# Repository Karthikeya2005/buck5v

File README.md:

# buck5v: 12 V to 5 V, 2 A Buck Converter (KiCad 10)

A 2-layer synchronous buck converter board built around the Texas Instruments **TPS54202**. Input is 9 to 24 V, output is 5 V at up to 2 A, with a switching frequency of about 500 kHz.

> **Status: designed and checked in software only.**
> The board has not been fabricated, assembled or measured. Every figure below is a calculation from the datasheet, not a bench result. Part sourcing (stock, LCSC numbers) was not verified either.

I built this to learn power-supply design end to end: choosing the IC, calculating each component, wiring the schematic, laying out the board around the switching loop, and checking it with ERC and DRC. I checked the datasheet values and reviewed the schematic, layout and DRC results myself.

## Specification

| Parameter | Value |
|---|---|
| Input voltage | 9 to 24 V (IC accepts 4.5 to 28 V) |
| Output voltage | 5 V (about 5.03 V typical) |
| Output current | 2 A |
| Switching frequency | 500 kHz typical (390 to 630 kHz) |
| Topology | Synchronous buck, integrated FETs |
| Board | 2 layers, 45 x 35 mm |
| Protection | Series Schottky for reverse polarity, EN divider as undervoltage lockout |

## Design

### IC: TPS54202DDCR
4.5 to 28 V input, 2 A, internal high-side and low-side FETs, so no external catch diode is needed. Datasheet values I used: feedback voltage VFB = 0.596 V (0.581 to 0.611 V), switching frequency 500 kHz, low-side current limit up to 4.3 A.

### Output voltage
Vout = VFB x (1 + R1 / R2) = 0.596 x (1 + 102 k / 13.7 k) = **5.03 V** typical.
Over the VFB tolerance the output spans 4.91 to 5.16 V. Both resistors are standard 1% values.

### Inductor
L = 15 uH (Sunlord MWSA1004S-150MT: 45 mOhm DCR max, Isat 5.6 A taken conservatively from the datasheet).

| Vin | Duty cycle | Ripple current (p-p) | Peak current at 2 A load |
|---|---|---|---|
| 9 V | 0.56 | 0.30 A | 2.15 A |
| 12 V | 0.42 | 0.39 A | 2.19 A |
| 24 V | 0.21 | 0.53 A | 2.26 A |

Ripple current = Vout x (1 - D) / (L x f). Peak current stays well below both the inductor's 5.6 A saturation current and the IC's 4.3 A maximum low-side limit.

### Capacitors
| Ref | Value | Role |
|---|---|---|
| C1, C2 | 10 uF 50 V X7R (1210) | Bulk input |
| C3 | 100 nF 50 V X7R (0603) | High-frequency input decoupling, placed at the VIN pin |
| C4 | 100 nF 50 V X7R (0603) | Bootstrap, BOOT to SW |
| C5, C6 | 22 uF 25 V X7R (1210) | Output |
| C7 | 75 pF C0G (0603), not populated | Optional feed-forward across R1 |

Ceramic capacitance falls with DC bias, so the effective output capacitance at 5 V is lower than 44 uF. Output ripple depends mostly on ESR and layout, so it has to be measured on a real board.

### Enable divider (undervoltage lockout)
R4 = 511 k from VIN to EN, R5 = 105 k from EN to GND. With the datasheet EN rising threshold of 1.21 V typical (1.28 V max), the converter starts at about **7.1 V** (7.5 V worst case) at the IC's VIN node. EN sees about 1.5 V at 9 V in and about 4.1 V at 24 V in. Check this against the datasheet's absolute maximum rating for EN before building.

### Reverse-polarity protection
D1 is an SS34 Schottky in series with the input. It costs roughly 0.5 V and about 0.6 W at 9 V in and 2 A out. A P-channel MOSFET would waste less power but needs extra parts.

## Bill of materials

| Ref | Value | Footprint |
|---|---|---|
| U1 | TPS54202DDCR | TSOT-23-6 (hand-solder variant) |
| L1 | 15 uH, MWSA1004S-150MT | Sunlord MWSA1004S |
| D1 | SS34 Schottky | SMA |
| C1, C2 | 10 uF 50 V X7R | 1210 |
| C3, C4 | 100 nF 50 V X7R | 0603 |
| C5, C6 | 22 uF 25 V X7R | 1210 |
| C7 | 75 pF C0G (DNP) | 0603 |
| R1 | 102 k 1% | 0603 |
| R2 | 13.7 k 1% | 0603 |
| R4 | 511 k 1% | 0603 |
| R5 | 105 k 1% | 0603 |
| J1, J2 | 2-pin screw terminal | 5.00 mm pitch |
| TP1 to TP4 | Test points: VIN, VOUT, SW, GND | 1.5 mm pad |

Ordering would need a fresh sourcing pass. Several part numbers (including the inductor) were not confirmed in stock, and the 5.00 mm terminal block should be matched to a real part.

## Layout notes

- The input capacitors sit at the IC's VIN pin. Because SW is between VIN and GND on the 6-pin package, the 100 nF cap's ground return is about 10 mm, so the loop is tight on the VIN side only.
- SW copper is short (about 13 mm in total including the test point). The boot-cap branch off the SW node is about 6 mm, longer than ideal.
- VIN and SW are necked down to 0.65 mm for the first 1.3 to 1.5 mm at the 0.95 mm pin pitch so the 0.25 mm clearance rule holds. Other power traces are 1.0 mm or wider.
- The feedback divider sits near the FB pin, away from SW and L1.
- The bottom layer is a GND plane with stitching vias. The EN trace runs on the bottom layer, short and clear of the switching nodes.
- The TSOT-23-6 has no thermal pad, so heat leaves through the GND pin copper. Thermal performance has not been verified.

## Verification

| Check | Result |
|---|---|
| ERC | 0 errors (PWR_FLAG symbols added to VIN, GND and +5V) |
| DRC | 0 errors, 0 unconnected items at the last run |
| DRC warnings | Mostly stitching vias flagged "not connected on one layer" (the top-layer GND zone only covers a small patch near the IC) and a few silkscreen overlaps |
| Schematic to board sync | No differences |

## Known limitations

- Not built or measured. No efficiency, ripple, thermal or EMI data.
- The top-layer GND pour should cover the whole board. As it stands, the stitching vias outside the patch near U1 only connect to the bottom plane.
- Component sourcing and the 5.00 mm terminal-block part are unverified.
- Ripple and thermal estimates depend on real capacitor ESR and copper area, which this design does not confirm.

## Test plan (if built)

| Test | Setup | What to look for |
|---|---|---|
| Power-up | Bench supply at 12 V, current limit 0.2 A, no load | 5.0 V on TP2, no oscillation or smoke |
| Output accuracy | 9, 12, 24 V in, no load and 2 A load | Output within about +/-3% of 5 V |
| Efficiency | 0.1, 0.25, 0.5, 1, 1.5, 2 A at 9, 12, 24 V | Measure Vin and Iin at the board terminals, Vout and Iout at the load |
| Output ripple | Scope on TP2 with spring ground at TP4, 20 MHz bandwidth | Ripple in mV, compare with the estimate |
| SW waveform | Scope on TP3 | Duty cycle, ringing, frequency near 500 kHz |
| Load step | 0.2 A to 2 A | Overshoot and recovery |
| Thermal | 2 A for 10 minutes, thermal camera or thermocouple | IC and inductor temperature rise |
| Start-up threshold | Slowly raise Vin from 0 | Converter starts near 7 to 7.6 V |

## Repository layout

```
buck5v.kicad_pro        KiCad project
buck5v.kicad_sch        Schematic
buck5v.kicad_pcb        PCB layout
buck5v.kicad_sym        Project symbol library (TPS54202)
sym-lib-table           Library table for the project symbol
docs/                   Images of the schematic, board and 3D view
fab/                    Gerber files, drill files and BOM (CSV)
buck5v-gerbers.zip      The fab/ folder zipped, ready to upload to a board house
```

Open `buck5v.kicad_pro` in KiCad 10 or newer.

## Tools

KiCad 10. Datasheet values were checked by hand against the TI TPS54202 and Sunlord MWSA-S datasheets.

## License

MIT. See [LICENSE](LICENSE). There is no warranty, and nobody has independently reviewed this design. Have it reviewed before building it or using it in anything that matters.

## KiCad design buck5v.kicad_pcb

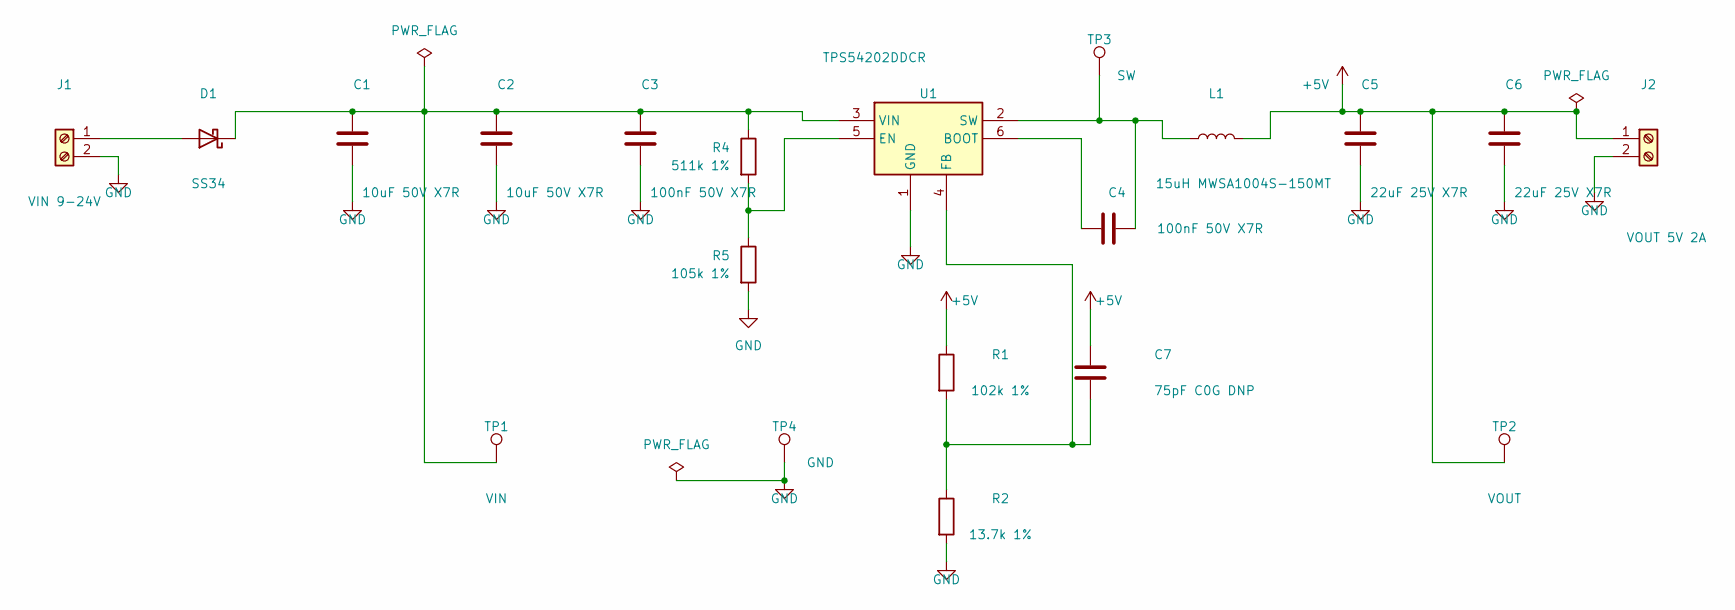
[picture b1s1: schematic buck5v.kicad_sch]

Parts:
C1, C2: 10uF 50V X7R; C_1210_3225Metric; MPN CL32B106KBJNNNE; LCSC C138687
C3, C4: 100nF 50V X7R; C_0603_1608Metric; MPN CL10B104KB8NNNC; LCSC C1591
C5, C6: 22uF 25V X7R; C_1210_3225Metric; MPN CL32B226KAJNNNE; LCSC C309062
C7: 75pF C0G DNP; C_0603_1608Metric
D1: SS34; D_SMA
J1: VIN 9-24V; TerminalBlock_MaiXu_MX126-5.0-02P_1x02_P5.00mm
J2: VOUT 5V 2A; TerminalBlock_MaiXu_MX126-5.0-02P_1x02_P5.00mm
L1: 15uH MWSA1004S-150MT; L_Sunlord_MWSA1004S; MPN MWSA1004S-150MT
R1: 102k 1%; R_0603_1608Metric
R2: 13.7k 1%; R_0603_1608Metric
R4: 511k 1%; R_0603_1608Metric
R5: 105k 1%; R_0603_1608Metric
TP1: VIN; TestPoint_Pad_D1.5mm
TP2: VOUT; TestPoint_Pad_D1.5mm
TP3: SW; TestPoint_Pad_D1.5mm
TP4: GND; TestPoint_Pad_D1.5mm
U1: TPS54202DDCR; TSOT-23-6_HandSoldering; MPN TPS54202DDCR; LCSC C191884

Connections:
+5V: C5.1, C6.1, C7.1, J2.1, L1.2, R1.1, TP2.1
GND: C1.2, C2.2, C3.2, C5.2, C6.2, J1.2, J2.2, R2.2, R5.2, TP4.1, U1.1 (GND)
unnamed: C1.1, C2.1, C3.1, D1.1 (K), R4.1, TP1.1, U1.3 (VIN)
unnamed: C4.1, U1.6 (BOOT)
unnamed: C4.2, L1.1, TP3.1, U1.2 (SW)
unnamed: C7.2, R1.2, R2.1, U1.4 (FB)
unnamed: D1.2 (A), J1.1
unnamed: R4.2, R5.1, U1.5 (EN)

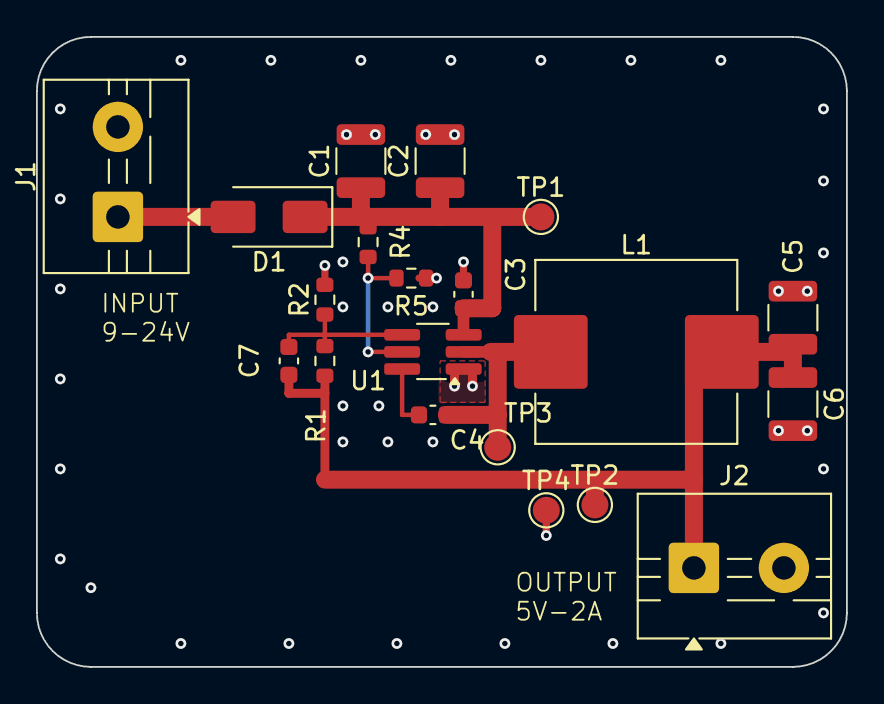
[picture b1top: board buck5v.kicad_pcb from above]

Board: 2 copper layers, 45.0 x 35.0 mm, 20 parts (0 on the bottom side), 8 nets.

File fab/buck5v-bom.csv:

"Id";"Designator";"Footprint";"Quantity";"Designation";"Supplier and ref";
1;"C1, C2";"C_1210_3225Metric";2;"10uF 50V X7R";;;
2;"C3, C4";"C_0603_1608Metric";2;"100nF 50V X7R";;;
3;"C5, C6";"C_1210_3225Metric";2;"22uF 25V X7R";;;
4;"C7";"C_0603_1608Metric";1;"75pF C0G DNP";;;
5;"D1";"D_SMA";1;"SS34";;;
6;"J1";"TerminalBlock_MaiXu_MX126-5.0-02P_1x02_P5.00mm";1;"VIN 9-24V";;;
7;"J2";"TerminalBlock_MaiXu_MX126-5.0-02P_1x02_P5.00mm";1;"VOUT 5V 2A";;;
8;"L1";"L_Sunlord_MWSA1004S";1;"15uH MWSA1004S-150MT";;;
9;"R1";"R_0603_1608Metric";1;"102k 1%";;;
10;"R2";"R_0603_1608Metric";1;"13.7k 1%";;;
11;"R4";"R_0603_1608Metric";1;"511k 1%";;;
12;"R5";"R_0603_1608Metric";1;"105k 1%";;;
13;"U1";"TSOT-23-6_HandSoldering";1;"TPS54202DDCR";;;
